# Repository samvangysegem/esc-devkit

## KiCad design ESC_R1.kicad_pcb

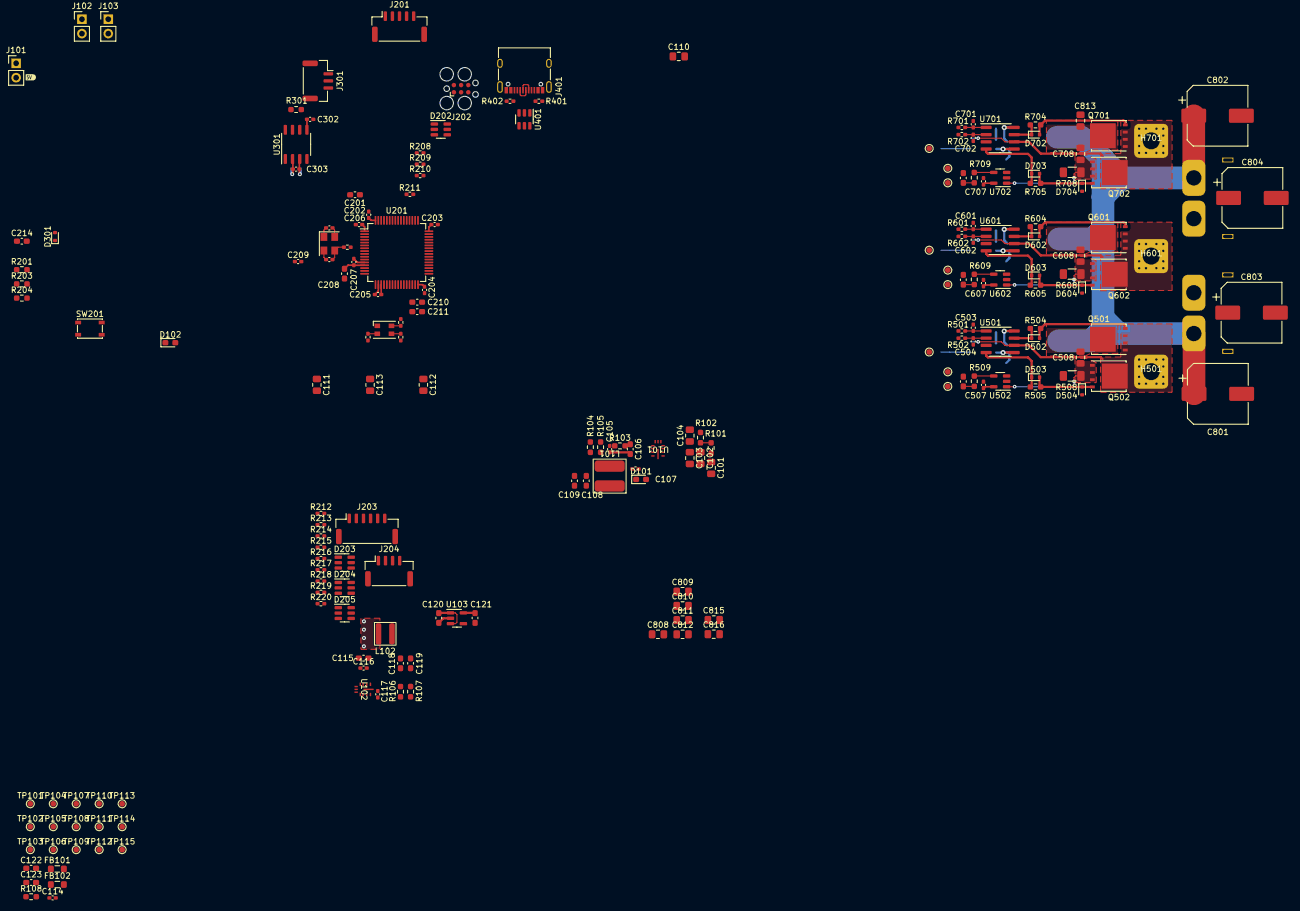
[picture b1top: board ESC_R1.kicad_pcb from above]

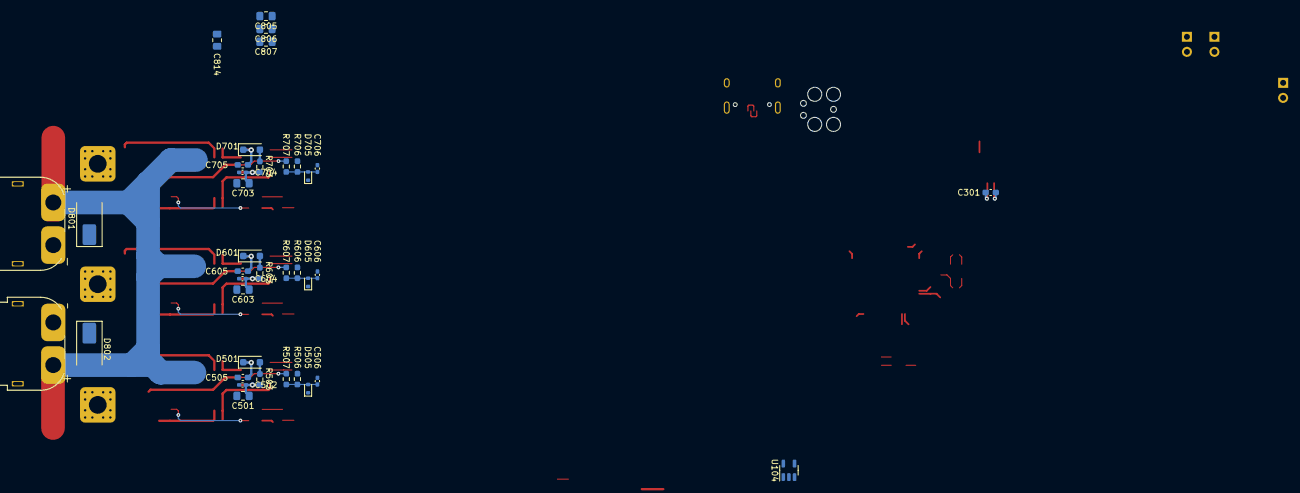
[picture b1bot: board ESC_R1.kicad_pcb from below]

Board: 4 copper layers, 230 parts (37 on the bottom side), 114 nets.

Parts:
C101, C102, C103, C104, C110, C111, C112, C113, C501, C603, C703, C805, C806, C807, C808, C809, C810, C811, C812, C813, C814, C815, C816: 2u2 50V; C_0805_2012Metric_Pad1.18x1.45mm_HandSolder
C105, C107, C114, C116, C502, C604, C704: 100n 50V; C_0402_1005Metric_Pad0.74x0.62mm_HandSolder
C106, C115: 1u 10V; C_0603_1608Metric_Pad1.08x0.95mm_HandSolder
C108, C109: 22u 25V; C_0603_1608Metric_Pad1.08x0.95mm_HandSolder
C117: 1.6p; C_0402_1005Metric_Pad0.74x0.62mm_HandSolder
C118, C119: 10u 10V; C_0603_1608Metric_Pad1.08x0.95mm_HandSolder
C120, C121, C122, C123, C201, C208, C210, C211, C301: 2u2 10V; C_0603_1608Metric_Pad1.08x0.95mm_HandSolder
C202, C203, C204, C205, C206, C207, C209, C302, C303, C503, C504, C507, C601, C602, C607, C701, C702, C707: 100n; C_0402_1005Metric_Pad0.74x0.62mm_HandSolder
C212, C213: 10p; C_0402_1005Metric_Pad0.74x0.62mm_HandSolder
C214, C505, C605, C705: 1u 50V; C_0603_1608Metric_Pad1.08x0.95mm_HandSolder
C506, C606, C706: DNP; C_0402_1005Metric_Pad0.74x0.62mm_HandSolder
C508, C608, C708: 100n 50V; C_0805_2012Metric_Pad1.18x1.45mm_HandSolder
C509, C609, C709: 10n; C_0603_1608Metric_Pad1.08x0.95mm_HandSolder
C801, C802, C803, C804: 150u; CP_Elec_10x10.5
D101, D102: GREEN; LED_0603_1608Metric_Pad1.05x0.95mm_HandSolder
D201: CLV1L-FKB; LED_Cree-PLCC4_3.2x2.8mm_CCW
D202, D205: ESDA6V1BC6; SOT-23-6
D203, D204: ESDA6V1-5SC6; SOT-23-6
D301, D502, D503, D504, D505, D602, D603, D604, D605, D702, D703, D704, D705: BAT41KFILM; D_SOD-523
D501, D601, D701: RB162MM-60; D_SOD-123F
D801, D802: SMBJ33CA-13-F; D_SMB_Handsoldering
FB101, FB102: 742792096; L_0805_2012Metric_Pad1.05x1.20mm_HandSolder
H501, H601, H701: Pad; HC_Phase_Pad_6x6
J101, J102, J103: Conn_01x02_Pin; PinHeader_1x02_P2.54mm_Vertical
J201: SM05B-GHS-TB; JST_GH_SM05B-GHS-TB_1x05-1MP_P1.25mm_Horizontal
J202: SWD TagConnect; Tag-Connect_TC2030-IDC-FP_2x03_P1.27mm_Vertical
J203: SM06B-GHS-TB; JST_GH_SM06B-GHS-TB_1x06-1MP_P1.25mm_Horizontal
J204: SM04B-GHS-TB; JST_GH_SM04B-GHS-TB_1x04-1MP_P1.25mm_Horizontal
J301: SM03B-GHS-TB; JST_GH_SM03B-GHS-TB_1x03-1MP_P1.25mm_Horizontal
J401: USB_C_Receptacle_USB2.0; USB_C_Receptacle_XKB_U262-16XN-4BVC11
J801: XT60PW-F; XT60PW-F_1x02_P7.20mm_Horizontal
J802: XT60PW-M; XT60PW-M_1x02_P7.20mm_Horizontal_WP
L101: 74408943150
L102: 74438357082
Q501, Q502, Q601, Q602, Q701, Q702: BSC072N08NS5; TDSON-8-1
R101: 100k; R_0603_1608Metric_Pad0.98x0.95mm_HandSolder
R102: 9.09k; R_0603_1608Metric_Pad0.98x0.95mm_HandSolder
R103: 54k9; R_0603_1608Metric_Pad0.98x0.95mm_HandSolder
R104, R201, R204: 10k; R_0603_1608Metric_Pad0.98x0.95mm_HandSolder
R105, R106: 0R5; R_0603_1608Metric_Pad0.98x0.95mm_HandSolder
R107: 2k4; R_0603_1608Metric_Pad0.98x0.95mm_HandSolder
R108: 1k; R_0603_1608Metric_Pad0.98x0.95mm_HandSolder
R202, R205: 150; R_0402_1005Metric_Pad0.72x0.64mm_HandSolder
R203: NTC 10k; R_0603_1608Metric_Pad0.98x0.95mm_HandSolder
R206, R207: 20; R_0402_1005Metric_Pad0.72x0.64mm_HandSolder
R208, R209, R210, R211, R212, R213, R214, R215, R216, R217, R218, R219, R220: 50; R_0402_1005Metric_Pad0.72x0.64mm_HandSolder
R301: 120; R_0603_1608Metric_Pad0.98x0.95mm_HandSolder
R401, R402: 5k1; R_0402_1005Metric_Pad0.72x0.64mm_HandSolder
R501, R502, R601, R602, R701, R702: 0R; R_0402_1005Metric_Pad0.72x0.64mm_HandSolder
R503, R603, R703: 30R1; R_0603_1608Metric_Pad0.98x0.95mm_HandSolder
R504, R505, R604, R605, R704, R705: 4R7; R_0603_1608Metric_Pad0.98x0.95mm_HandSolder
R506, R606, R706: 2k2; R_0603_1608Metric_Pad0.98x0.95mm_HandSolder
R507, R607, R707: 17k8; R_0603_1608Metric_Pad0.98x0.95mm_HandSolder
R508, R608, R708: 0.001; R_1206_3216Metric_Pad1.30x1.75mm_HandSolder
R509, R609, R709: 100; R_0603_1608Metric_Pad0.98x0.95mm_HandSolder
SW201: PTS810 SJK; SW_SPST_PTS810
TP101, TP102: VBAT; TestPoint_Pad_D1.0mm
TP103: FILT_VIN_12V; TestPoint_Pad_D1.0mm
TP104: FILT_VIN_5V; TestPoint_Pad_D1.0mm
TP105: FILT_VIN_3V3A; TestPoint_Pad_D1.0mm
TP106: FILT_VIN_3V3; TestPoint_Pad_D1.0mm
TP107: 12V; TestPoint_Pad_D1.0mm
TP108: 5V; TestPoint_Pad_D1.0mm
TP109: 3V3; TestPoint_Pad_D1.0mm
TP110: 3V3A; TestPoint_Pad_D1.0mm
TP111, TP112, TP113, TP114, TP115, TP503, TP603, TP703: GND; TestPoint_Pad_D1.0mm
TP501, TP601, TP701: PH_CURR_F; TestPoint_Pad_D1.0mm
TP502, TP602, TP702: PH_VSDIV; TestPoint_Pad_D1.0mm
U101, U102: LMR36006; RNX0012B
U103, U104: TLV75533PDBV; SOT-23-5
U201: STM32F446RETx; LQFP-64_10x10mm_P0.5mm
U301: TJA1441AT; SO-8_3.9x4.9mm_P1.27mm
U401: USBLC6-2SC6; SOT-23-6
U501, U601, U701: IR2171S; SOIC-8_3.9x4.9mm_P1.27mm
U502, U602, U702: INA180B2; SOT-23-5
Y201: 16MHz; Crystal_SMD_SeikoEpson_FA238V-4Pin_3.2x2.5mm
kibuzzard-65860F08: G***; kibuzzard-65860F08

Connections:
+3.3V: C123.1, C201.1, C202.1, C203.1, C204.1, C205.1, C206.1, C302.1, D102.2 (A), D201.1 (A), D202.6 (CH4), D203.6 (IO5), D204.6 (IO5), D205.6 (CH4), D301.1 (K), D505.1 (K), D605.1 (K), D705.1 (K), J103.2, J201.1, J202.1 (VCC), J203.1, J204.1, R203.1, TP109.1, U104.5 (OUT), U201.1 (VBAT), U201.19 (VDD), U201.32 (VDD), U201.48 (VDD), U201.64 (VDD), U301.5 (VIO)
+3.3VA: C121.1, C207.1, C208.1, C507.1, C607.1, C707.1, TP110.1, U103.5 (OUT), U201.13 (VDDA), U502.5 (V+), U602.5 (V+), U702.5 (V+)
+5V: C117.2, C118.1, C119.1, C301.1, C303.1, D101.2 (A), J102.2, L102.2, R103.2, R105.2, R106.2, TP108.1, U301.3 (VCC)
+12V: C108.1, C109.1, C501.1, C502.2, C603.1, C604.2, C703.1, C704.2, J101.2, L101.2, R101.2, R503.1, R603.1, R703.1, TP107.1, U501.5 (VCC), U601.5 (VCC), U701.5 (VCC)
+BATT: C101.1, C110.1, C508.1, C608.1, C708.1, C801.1, C802.1, C803.1, C804.1, C805.1, C806.1, C807.1, C808.1, C809.1, C810.1, C811.1, C812.1, C813.1, C814.1, C815.1, C816.1, D801.2 (A2), D802.2 (A2), FB101.1, FB102.1, J801.2 (VIN), J802.2 (VIN), Q501.5 (D), Q601.5 (D), Q701.5 (D), TP101.1, TP102.1
/[1] Power Supply/3V3_LED_K: D102.1 (K), R108.2
/[1] Power Supply/5V_LED_K: D101.1 (K), R107.2
/[1] Power Supply/FILT_VIN_3V3: C122.1, R106.1, TP106.1, U104.1 (IN), U104.3 (EN)
/[1] Power Supply/FILT_VIN_3V3A: C120.1, R105.1, TP105.1, U103.1 (IN), U103.3 (EN)
/[1] Power Supply/FILT_VIN_5V: C111.1, C112.1, C113.1, C114.1, FB102.2, TP104.1, U102.2 (VIN), U102.9 (EN), U102.10 (VIN)
/[1] Power Supply/FILT_VIN_12V: C102.1, C103.1, C104.1, C105.1, FB101.2, TP103.1, U101.2 (VIN), U101.9 (EN), U101.10 (VIN)
/[1] Power Supply/VFB_5V: C117.1, R103.1, R104.2, U102.7 (FB)
/[1] Power Supply/VFB_12V: R101.1, R102.2, U101.7 (FB)
/[1] Power Supply/VSW_5V: C116.1, L102.1, U102.3 (NC), U102.12 (SW)
/[1] Power Supply/VSW_12V: C107.1, L101.1, U101.3 (NC), U101.12 (SW)
/[2] MCU/BOOT0: R201.1, U201.60 (BOOT0)
/[2] MCU/ENC_A: R210.1, U201.58 (PB6)
/[2] MCU/ENC_B: R209.1, U201.59 (PB7)
/[2] MCU/ENC_Z: R208.1, U201.57 (PB5)
/[2] MCU/HSE_IN: C212.1, U201.5 (PH0), Y201.1
/[2] MCU/HSE_OUT: R202.2, U201.6 (PH1)
/[2] MCU/LED_B: R207.1, U201.26 (PB0)
/[2] MCU/LED_G: R206.1, U201.27 (PB1)
/[2] MCU/LED_R: R205.1, U201.23 (PA7)
/[2] MCU/NRST: C209.1, R211.1, SW201.2, U201.7 (NRST)
/[2] MCU/PHA_CURR_FILT: C509.2, R509.1, TP501.1, U201.17 (PA3)
/[2] MCU/PHA_HIN: R501.1, U201.41 (PA8)
/[2] MCU/PHA_LIN: R502.1, U201.34 (PB13)
/[2] MCU/PHA_VSDIV: C506.2, D505.2 (A), R506.1, R507.1, TP502.1, U201.14 (PA0)
/[2] MCU/PHB_CURR_FILT: C609.2, R609.1, TP601.1, U201.20 (PA4)
/[2] MCU/PHB_HIN: R601.1, U201.42 (PA9)
/[2] MCU/PHB_LIN: R602.1, U201.35 (PB14)
/[2] MCU/PHB_VSDIV: C606.2, D605.2 (A), R606.1, R607.1, TP602.1, U201.15 (PA1)
/[2] MCU/PHC_CURR_FILT: C709.2, R709.1, TP701.1, U201.21 (PA5)
/[2] MCU/PHC_HIN: R701.1, U201.43 (PA10)
/[2] MCU/PHC_LIN: R702.1, U201.36 (PB15)
/[2] MCU/PHC_VSDIV: C706.2, D705.2 (A), R706.1, R707.1, TP702.1, U201.16 (PA2)
/[2] MCU/RGB_B: D201.4 (BK), R207.2
/[2] MCU/RGB_G: D201.3 (GK), R206.2
/[2] MCU/RGB_R: D201.2 (RK), R205.2
/[2] MCU/SPI_CLK: R215.1, U201.51 (PC10)
/[2] MCU/SPI_CS: R218.1, U201.50 (PA15)
/[2] MCU/SPI_MISO: R216.1, U201.52 (PC11)
/[2] MCU/SPI_MOSI: R217.1, U201.53 (PC12)
/[2] MCU/SYS_SWDCLK: R212.1, U201.49 (PA14)
/[2] MCU/SYS_SWDIO: R213.1, U201.46 (PA13)
/[2] MCU/SYS_SWO: R214.1, U201.55 (PB3)
/[2] MCU/TC_NRST: D203.5 (IO4), J202.3 (~RESET), R211.2
/[2] MCU/TC_SYS_SWDCLK: D203.4 (IO3), J202.4 (SWCLK), R212.2
/[2] MCU/TC_SYS_SWDIO: D203.3 (IO2), J202.2 (SWDIO), R213.2
/[2] MCU/TC_SYS_SWO: D203.1 (IO1), J202.6 (SWO), R214.2
/[2] MCU/TEMP: C214.1, D301.2 (A), R203.2, R204.1, U201.22 (PA6)
/[2] MCU/USART_RX: R220.1, U201.25 (PC5)
/[2] MCU/USART_TX: R219.1, U201.29 (PB10)
/[2] MCU/VCAP1: C210.1, C211.1, U201.30 (VCAP_1)
/[2] MCU/XTAL_IN: C213.1, R202.1, Y201.3
/[3] CAN/CAN+: J301.1, R301.2, U301.7 (CANH)
/[3] CAN/CAN-: J301.2, R301.1, U301.6 (CANL)
/[4] USB/USB_CC1: J401.A5 (CC1), R401.1
/[4] USB/USB_CC2: J401.B5 (CC2), R402.1
/[4] USB/USB_CONN_D+: J401.A6 (D+), J401.B6 (D+), U401.3 (I/O2)
/[4] USB/USB_CONN_D-: J401.A7 (D-), J401.B7 (D-), U401.1 (I/O1)
/[4] USB/USB_VBUS: J401.A4 (VBUS), J401.A9 (VBUS), J401.B4 (VBUS), J401.B9 (VBUS), U401.5 (VBUS)
/[5] 3-Phase Bridge - Phase A/PH_CIN+: C508.2, Q502.1 (S), Q502.2 (S), Q502.3 (S), R508.2, U502.1 (+)
/[5] 3-Phase Bridge - Phase A/PH_CURR: R509.2, U502.4
/[5] 3-Phase Bridge - Phase A/PH_HOUT: D502.1 (K), R504.1, U501.7 (HO)
/[5] 3-Phase Bridge - Phase A/PH_HOUT_G: D502.2 (A), Q501.4 (G), R504.2
/[5] 3-Phase Bridge - Phase A/PH_IR_HIN: C503.1, R501.2, U501.1 (HIN)
/[5] 3-Phase Bridge - Phase A/PH_IR_LIN: C504.1, R502.2, U501.2 (LIN)
/[5] 3-Phase Bridge - Phase A/PH_LOUT: D503.1 (K), R505.1, U501.4 (LO)
/[5] 3-Phase Bridge - Phase A/PH_LOUT_G: D503.2 (A), D504.1 (K), Q502.4 (G), R505.2
/[5] 3-Phase Bridge - Phase A/PH_VB: C505.1, D501.1 (K), U501.8 (VB)
/[5] 3-Phase Bridge - Phase A/PH_VRD: D501.2 (A), R503.2
/[5] 3-Phase Bridge - Phase A/PH_VS: C505.2, H501.1, Q501.1 (S), Q501.2 (S), Q501.3 (S), Q502.5 (D), R507.2, U501.6 (VS)
/[6] 3-Phase Bridge - Phase B/PH_CIN+: C608.2, Q602.1 (S), Q602.2 (S), Q602.3 (S), R608.2, U602.1 (+)
/[6] 3-Phase Bridge - Phase B/PH_CURR: R609.2, U602.4
/[6] 3-Phase Bridge - Phase B/PH_HOUT: D602.1 (K), R604.1, U601.7 (HO)
/[6] 3-Phase Bridge - Phase B/PH_HOUT_G: D602.2 (A), Q601.4 (G), R604.2
/[6] 3-Phase Bridge - Phase B/PH_IR_HIN: C601.1, R601.2, U601.1 (HIN)
/[6] 3-Phase Bridge - Phase B/PH_IR_LIN: C602.1, R602.2, U601.2 (LIN)
/[6] 3-Phase Bridge - Phase B/PH_LOUT: D603.1 (K), R605.1, U601.4 (LO)
/[6] 3-Phase Bridge - Phase B/PH_LOUT_G: D603.2 (A), D604.1 (K), Q602.4 (G), R605.2
/[6] 3-Phase Bridge - Phase B/PH_VB: C605.1, D601.1 (K), U601.8 (VB)
/[6] 3-Phase Bridge - Phase B/PH_VRD: D601.2 (A), R603.2
/[6] 3-Phase Bridge - Phase B/PH_VS: C605.2, H601.1, Q601.1 (S), Q601.2 (S), Q601.3 (S), Q602.5 (D), R607.2, U601.6 (VS)
/[7] 3-Phase Bridge - Phase C/PH_CIN+: C708.2, Q702.1 (S), Q702.2 (S), Q702.3 (S), R708.2, U702.1 (+)
/[7] 3-Phase Bridge - Phase C/PH_CURR: R709.2, U702.4
/[7] 3-Phase Bridge - Phase C/PH_HOUT: D702.1 (K), R704.1, U701.7 (HO)
/[7] 3-Phase Bridge - Phase C/PH_HOUT_G: D702.2 (A), Q701.4 (G), R704.2
/[7] 3-Phase Bridge - Phase C/PH_IR_HIN: C701.1, R701.2, U701.1 (HIN)
/[7] 3-Phase Bridge - Phase C/PH_IR_LIN: C702.1, R702.2, U701.2 (LIN)
/[7] 3-Phase Bridge - Phase C/PH_LOUT: D703.1 (K), R705.1, U701.4 (LO)
/[7] 3-Phase Bridge - Phase C/PH_LOUT_G: D703.2 (A), D704.1 (K), Q702.4 (G), R705.2
/[7] 3-Phase Bridge - Phase C/PH_VB: C705.1, D701.1 (K), U701.8 (VB)
/[7] 3-Phase Bridge - Phase C/PH_VRD: D701.2 (A), R703.2
/[7] 3-Phase Bridge - Phase C/PH_VS: C705.2, H701.1, Q701.1 (S), Q701.2 (S), Q701.3 (S), Q702.5 (D), R707.2, U701.6 (VS)
CAN_RXD: U201.61 (PB8), U301.4 (RXD)
CAN_TXD: U201.62 (PB9), U301.1 (TXD)
GND: C101.2, C102.2, C103.2, C104.2, C105.2, C106.2, C108.2, C109.2, C110.2, C111.2, C112.2, C113.2, C114.2, C115.2, C118.2, C119.2, C120.2, C121.2, C122.2, C123.2, C201.2, C202.2, C203.2, C204.2, C205.2, C206.2, C207.2, C208.2, C209.2, C210.2, C211.2, C212.2, C213.2, C214.2, C301.2, C302.2, C303.2, C501.2, C502.1, C503.2, C504.2, C506.1, C507.2, C509.1, C601.2, C602.2, C603.2, C604.1, C606.1, C607.2, C609.1, C701.2, C702.2, C703.2, C704.1, C706.1, C707.2, C709.1, C801.2, C802.2, C803.2, C804.2, C805.2, C806.2, C807.2, C808.2, C809.2, C810.2, C811.2, C812.2, C813.2, C814.2, C815.2, C816.2, D202.2 (GND), D202.5 (GND), D203.2 (GND), D204.2 (GND), D205.2 (GND), D205.5 (GND), D504.2 (A), D604.2 (A), D704.2 (A), D801.1 (A1), D802.1 (A1), J101.1, J102.1, J103.1, J201.5, J202.5 (GND), J203.6, J204.4, J301.3, J401.A1 (GND), J401.A12 (GND), J401.B1 (GND), J401.B12 (GND), J401.S1 (SHIELD), J801.1 (GND), J802.1 (GND), R102.1, R104.1, R107.1, R108.1, R201.2, R204.2, R401.2, R402.2, R506.2, R508.1, R606.2, R608.1, R706.2, R708.1, SW201.1, TP111.1, TP112.1, TP113.1, TP114.1, TP115.1, TP503.1, TP603.1, TP703.1, U101.1 (PGND), U101.6 (AGND), U101.11 (PGND), U102.1 (PGND), U102.6 (AGND), U102.11 (PGND), U103.2 (GND), U104.2 (GND), U201.12 (VSSA), U201.18 (VSS), U201.31 (VSS), U201.47 (VSS), U201.63 (VSS), U301.2 (GND), U301.8 (S), U401.2 (GND), U501.3 (COM), U502.2 (GND), U502.3 (-), U601.3 (COM), U602.2 (GND), U602.3 (-), U701.3 (COM), U702.2 (GND), U702.3 (-), Y201.2, Y201.4
unnamed: D202.1 (CH1), J201.4, R210.2
unnamed: D202.3 (CH2), J201.3, R209.2
unnamed: D202.4 (CH3), J201.2, R208.2
unnamed: D204.1 (IO1), J203.5, R218.2
unnamed: D204.3 (IO2), J203.4, R217.2
unnamed: D204.4 (IO3), J203.3, R216.2
unnamed: D204.5 (IO4), J203.2, R215.2
unnamed: D205.3 (CH2), J204.3, R220.2
unnamed: D205.4 (CH3), J204.2, R219.2
unnamed: C107.2, U101.4 (BOOT)
unnamed: C106.1, U101.5 (VCC)
unnamed: C116.2, U102.4 (BOOT)
unnamed: C115.1, U102.5 (VCC)
USB_D+: U201.45 (PA12), U401.4 (I/O2)
USB_D-: U201.44 (PA11), U401.6 (I/O1)

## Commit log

2022-11-07 chore: initial commit
2022-11-07 chore: updating folder structure
2022-11-07 chore: updated gitignore to folder structure
2022-11-07 chore: updated readme file
2022-11-07 fix: updated readme naming
2022-11-07 chore: updated file structure
2023-04-18 feat: added power source schematics and updated capacitor values
2023-05-01 feat: power supply updates and mcu kickoff
2023-05-02 feat/chore: MCU supply caps and filter circuitry and updated component references in power supply sheet
2023-05-17 feat: initial peripheral circuitry for MCU
2023-05-18 feat: oscillator design
2023-06-23 reset button and SWD tag connect
2023-06-25 swd protection
2023-06-26 global labels to local labels wherever possible and mcu pinout addition
2023-06-26 todo list update
2023-07-05 check ESD protection for CAN and SWD bus
2023-07-21 verified Timer 1 functionality for motor control
2023-11-18 feat: USB circuitry
2023-11-18 chore: updated links and footprints
2023-11-20 feat: 5V power supply selection
2023-11-20 feat: rgb led
2023-11-24 feat: new phases, LED pins
2023-11-25 feat: LED routing, encoder interface, footprint updates
2023-11-26 feat: footprint assignment, circuit check and routing kickoff
2023-11-28 feat: initial layout of phase C
2023-12-17 feat: component placement for 1 phase completed
2023-12-19 fix: fixed LTSpice simulation and updated track widths accordingly
2023-12-24 feat: single phase, HSE, CAN routing and general layout
2024-01-01 feat: major circuit rework, style update and addition of a few extra subcomponents
2024-01-02 feat: component placement, again
2024-01-10 chore: project update
2024-01-22 feat: finished inverter placement and routing
